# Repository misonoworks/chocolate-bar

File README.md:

# Chocolate Bar

A low-profile 50% keyboard, with less ergonomics than expected!

This keyboard uses choc switches. Choc switches are low-profile switches pioneered by Kailh that use a non-MX style stem. This keyboard uses only standard sizes for choc keycaps, being 1u, 1.5u, and 2u

Please note: V2 PCBs are still compatible with V1 cases and plates. The new feature on the V2 PCB, the OLED, cannot be used on V1 plates or cases. V2 cases do not exist yet, that is currently still being worked on.
V2 firmware is similarly unavailable, though the current firmware should work provided you update the pins. This will be updated after the next proto run.

## Layout

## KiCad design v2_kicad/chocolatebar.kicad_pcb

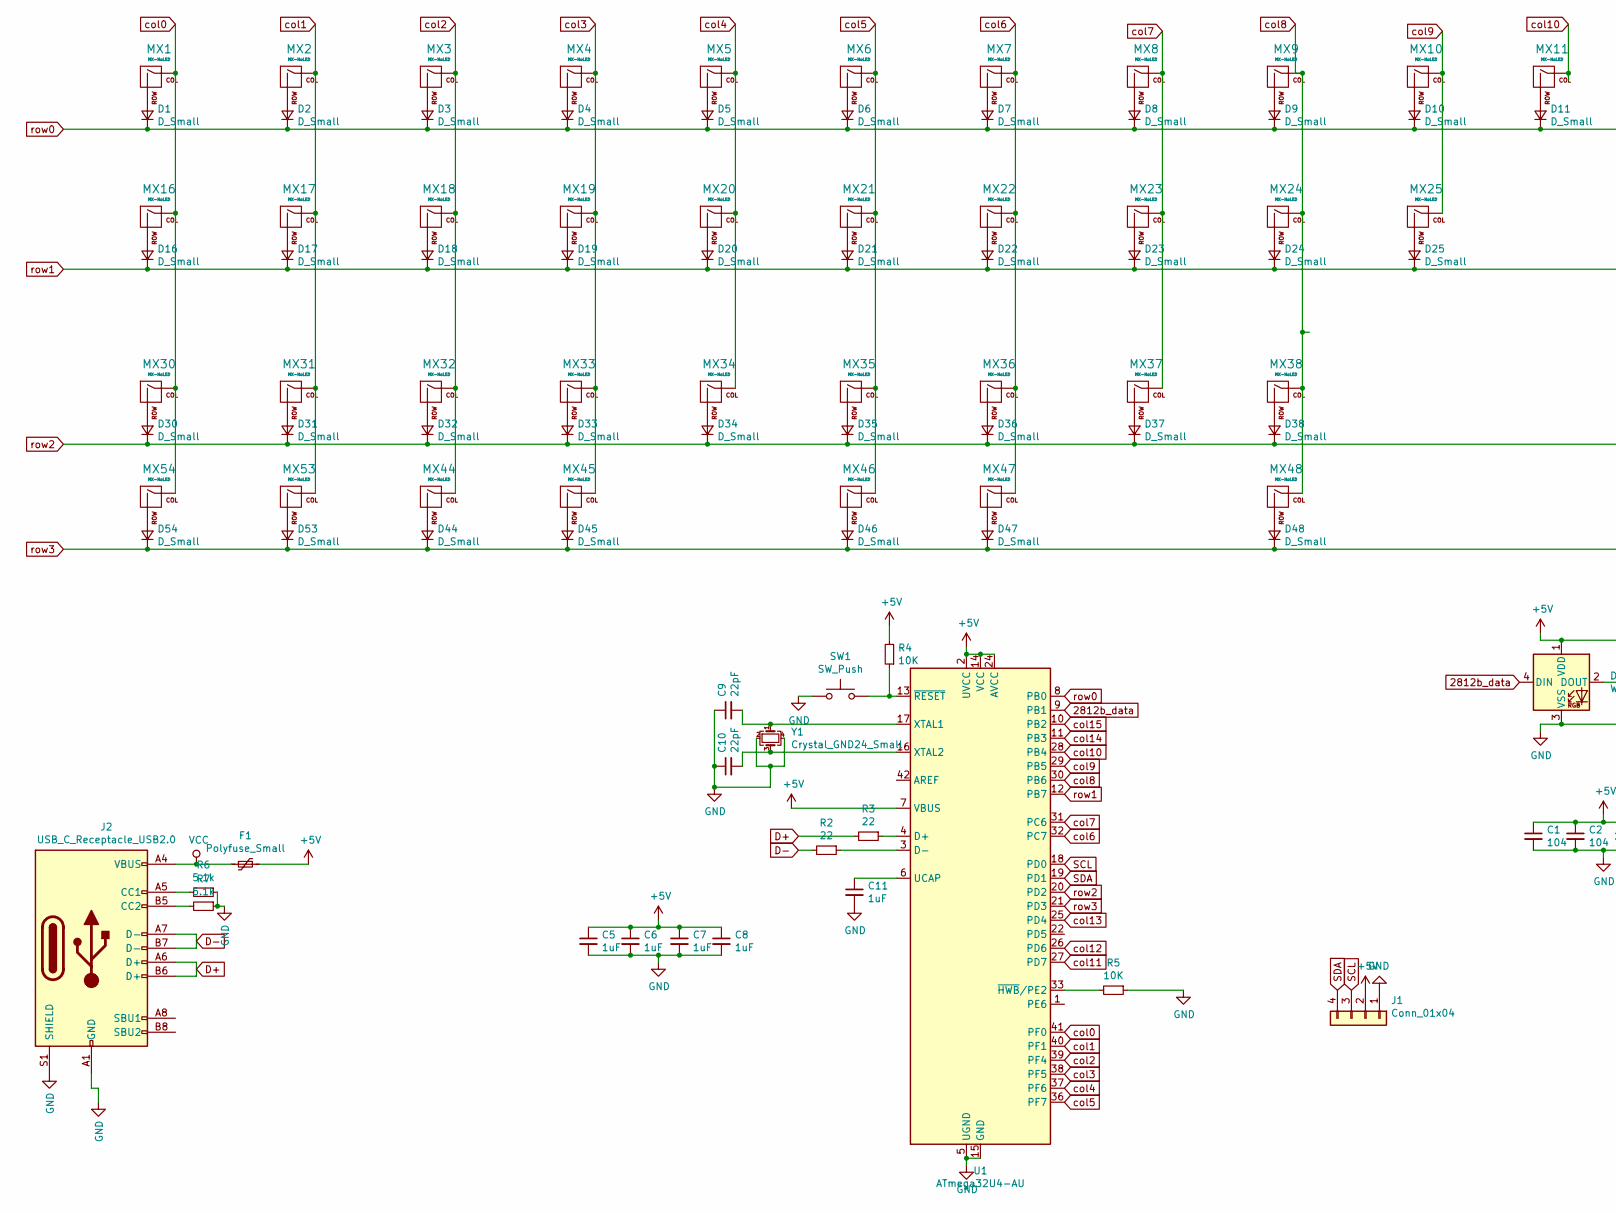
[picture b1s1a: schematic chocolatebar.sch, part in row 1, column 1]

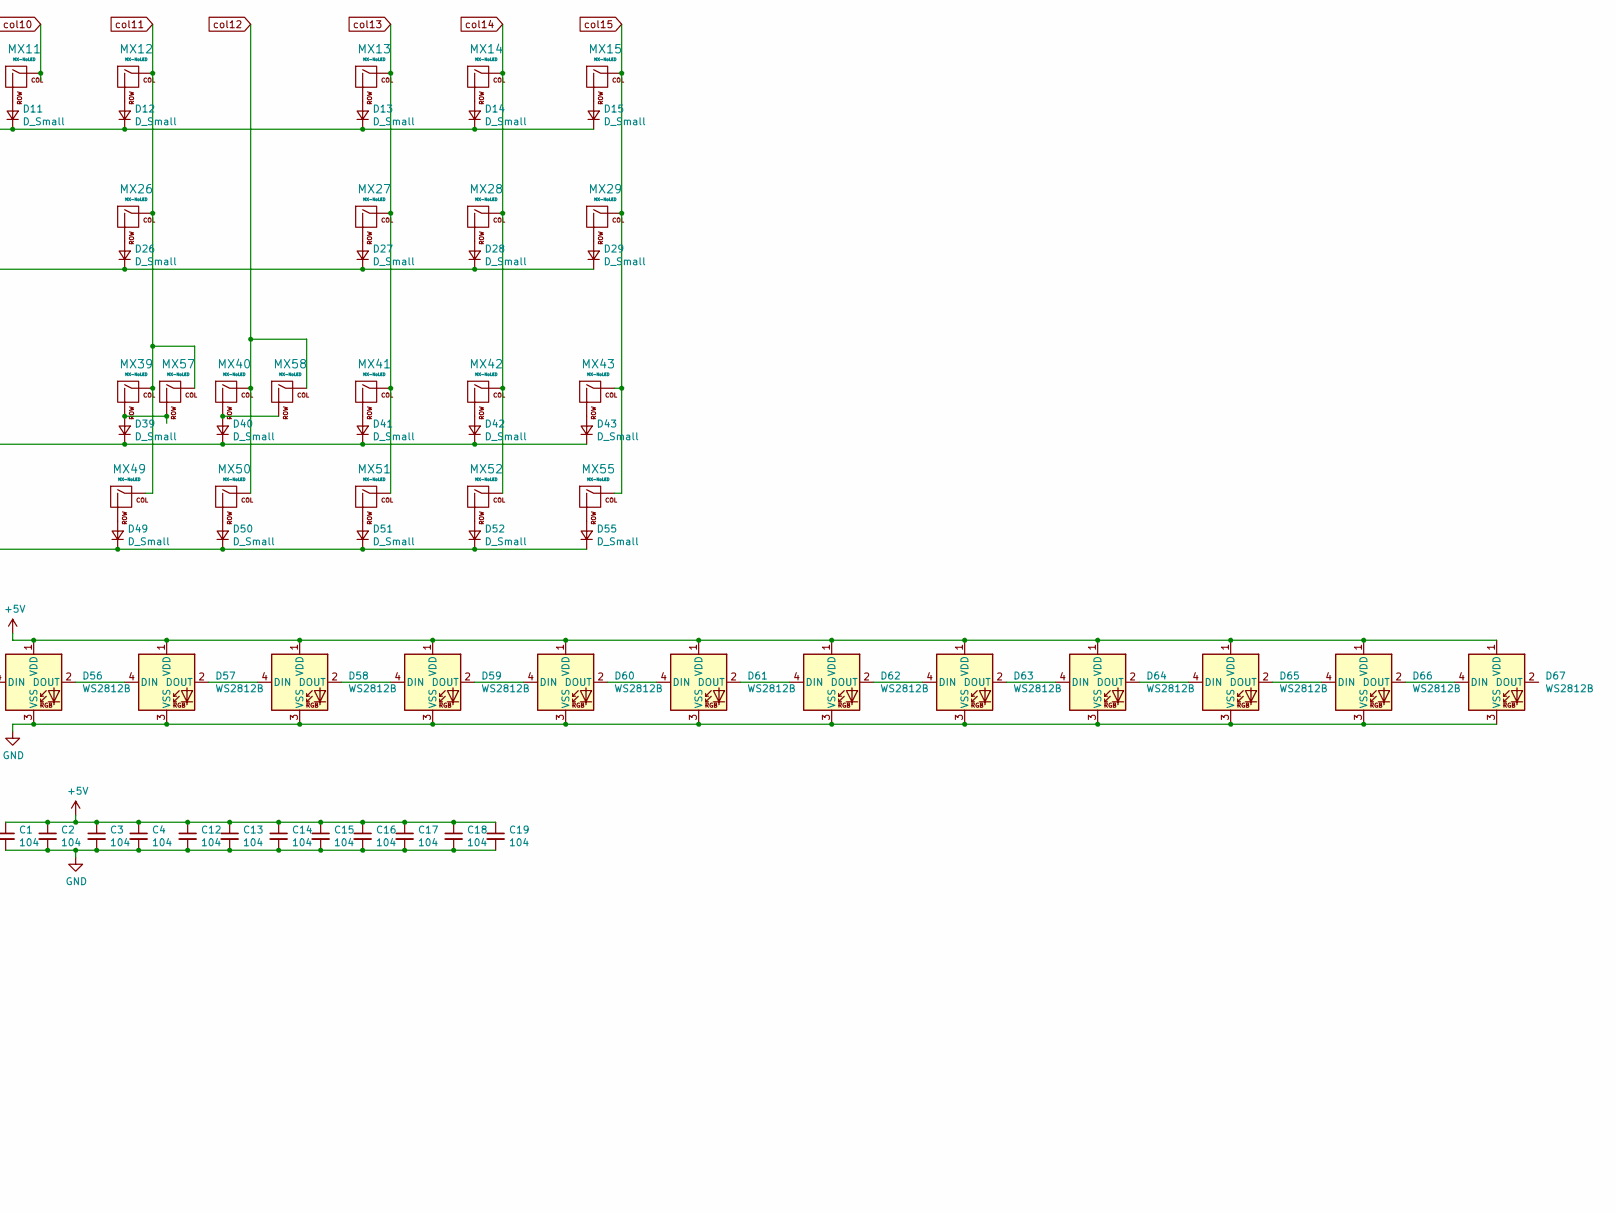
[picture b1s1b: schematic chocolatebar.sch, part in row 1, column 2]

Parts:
C1, C2, C3, C4, C12, C13, C14, C15, C16, C17, C18, C19: 104; C_0805_2012Metric
C5, C6, C7, C8, C11: 1uF; C_0805_2012Metric
C9, C10: 22pF; C_0805_2012Metric
D1, D2, D3, D4, D5, D6, D7, D8, D9, D10, D11, D12, D13, D14, D15, D16, D17, D18, D19, D20, D21, D22, D23, D24, D25, D26, D27, D28, D29, D30, D31, D32, D33, D34, D35, D36, D37, D38, D39, D40, D41, D42, D43, D44, D45, D46, D47, D48, D49, D50, D51, D52, D53, D54, D55: D_Small; D_SOD-123
D56, D57, D58, D59, D60, D61, D62, D63, D64, D65, D66, D67: WS2812B; LED_WS2812B_PLCC4_5.0x5.0mm_P3.2mm
F1: Polyfuse_Small; Fuse_1206_3216Metric
J1: Conn_01x04; PinSocket_1x04_P2.54mm_Vertical
J2: USB_C_Receptacle_USB2.0; USB_C_Receptacle_HRO_TYPE-C-31-M-12
MX1, MX2, MX3, MX4, MX5, MX6, MX7, MX8, MX9, MX10, MX11, MX12, MX13, MX14, MX15, MX16, MX17, MX18, MX19, MX20, MX21, MX22, MX23, MX24, MX25, MX27, MX28, MX29, MX31, MX32, MX33, MX34, MX35, MX36, MX37, MX38, MX39, MX40, MX41, MX42, MX43, MX44, MX47, MX49, MX50, MX51, MX52, MX57, MX58: MX-NoLED; Kailh-PG1350-1u-NoLED
MX26, MX48, MX53, MX54, MX55: MX-NoLED; Kailh-PG1350-1.5u
MX30, MX45, MX46: MX-NoLED; Kailh-PG1350-2u-NoLED
R2, R3: 22; R_0805_2012Metric
R4, R5: 10K; R_0805_2012Metric
R6, R7: 5.1k; R_0805_2012Metric
SW1: SW_Push; SKQG-1155865
U1: ATmega32U4-AU; TQFP-44_10x10mm_P0.8mm
Y1: Crystal_GND24_Small; Crystal_SMD_3225-4Pin_3.2x2.5mm

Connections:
2812b_data: D56.4 (DIN), U1.9 (PB1)
+5V: C1.1, C2.1, C3.1, C4.1, C5.1, C6.1, C7.1, C8.1, C12.1, C13.1, C14.1, C15.1, C16.1, C17.1, C18.1, C19.1, D56.1 (VDD), D57.1 (VDD), D58.1 (VDD), D59.1 (VDD), D60.1 (VDD), D61.1 (VDD), D62.1 (VDD), D63.1 (VDD), D64.1 (VDD), D65.1 (VDD), D66.1 (VDD), D67.1 (VDD), F1.1, J1.2, R4.2, U1.2 (UVCC), U1.7 (VBUS), U1.14 (VCC), U1.24 (AVCC), U1.34 (VCC), U1.44 (AVCC)
D+: J2.A6 (D+), J2.B6 (D+), R3.2
D-: J2.A7 (D-), J2.B7 (D-), R2.2
GND: C1.2, C2.2, C3.2, C4.2, C5.2, C6.2, C7.2, C8.2, C9.1, C10.1, C11.2, C12.2, C13.2, C14.2, C15.2, C16.2, C17.2, C18.2, C19.2, D56.3 (VSS), D57.3 (VSS), D58.3 (VSS), D59.3 (VSS), D60.3 (VSS), D61.3 (VSS), D62.3 (VSS), D63.3 (VSS), D64.3 (VSS), D65.3 (VSS), D66.3 (VSS), D67.3 (VSS), J1.1, J2.A1 (GND), J2.A12 (GND), J2.B1 (GND), J2.B12 (GND), J2.S1 (SHIELD), R5.1, R6.1, R7.1, SW1.1, U1.5 (UGND), U1.15 (GND), U1.23 (GND), U1.35 (GND), U1.43 (GND), Y1.2, Y1.4
unnamed: C9.2, U1.17 (XTAL1), Y1.1
unnamed: C10.2, U1.16 (XTAL2), Y1.3
unnamed: C11.1, U1.6 (UCAP)
unnamed: D1.2 (A), MX1.2 (ROW)
unnamed: D2.2 (A), MX2.2 (ROW)
unnamed: D3.2 (A), MX3.2 (ROW)
unnamed: D4.2 (A), MX4.2 (ROW)
unnamed: D5.2 (A), MX5.2 (ROW)
unnamed: D6.2 (A), MX6.2 (ROW)
unnamed: D7.2 (A), MX7.2 (ROW)
unnamed: D8.2 (A), MX8.2 (ROW)
unnamed: D9.2 (A), MX9.2 (ROW)
unnamed: D10.2 (A), MX10.2 (ROW)
unnamed: D11.2 (A), MX11.2 (ROW)
unnamed: D12.2 (A), MX12.2 (ROW)
unnamed: D13.2 (A), MX13.2 (ROW)
unnamed: D14.2 (A), MX14.2 (ROW)
unnamed: D15.2 (A), MX15.2 (ROW)
unnamed: D16.2 (A), MX16.2 (ROW)
unnamed: D17.2 (A), MX17.2 (ROW)
unnamed: D18.2 (A), MX18.2 (ROW)
unnamed: D19.2 (A), MX19.2 (ROW)
unnamed: D20.2 (A), MX20.2 (ROW)
unnamed: D21.2 (A), MX21.2 (ROW)
unnamed: D22.2 (A), MX22.2 (ROW)
unnamed: D23.2 (A), MX23.2 (ROW)
unnamed: D24.2 (A), MX24.2 (ROW)
unnamed: D25.2 (A), MX25.2 (ROW)
unnamed: D26.2 (A), MX26.2 (ROW)
unnamed: D27.2 (A), MX27.2 (ROW)
unnamed: D28.2 (A), MX28.2 (ROW)
unnamed: D29.2 (A), MX29.2 (ROW)
unnamed: D30.2 (A), MX30.2 (ROW)
unnamed: D31.2 (A), MX31.2 (ROW)
unnamed: D32.2 (A), MX32.2 (ROW)
unnamed: D33.2 (A), MX33.2 (ROW)
unnamed: D34.2 (A), MX34.2 (ROW)
unnamed: D35.2 (A), MX35.2 (ROW)
unnamed: D36.2 (A), MX36.2 (ROW)
unnamed: D37.2 (A), MX37.2 (ROW)
unnamed: D38.2 (A), MX38.2 (ROW)
unnamed: D39.2 (A), MX39.2 (ROW), MX57.2 (ROW)
unnamed: D40.2 (A), MX40.2 (ROW), MX58.2 (ROW)
unnamed: D41.2 (A), MX41.2 (ROW)
unnamed: D42.2 (A), MX42.2 (ROW)
unnamed: D43.2 (A), MX43.2 (ROW)
unnamed: D44.2 (A), MX44.2 (ROW)
unnamed: D45.2 (A), MX45.2 (ROW)
unnamed: D46.2 (A), MX46.2 (ROW)
unnamed: D47.2 (A), MX47.2 (ROW)
unnamed: D48.2 (A), MX48.2 (ROW)
unnamed: D49.2 (A), MX49.2 (ROW)
unnamed: D50.2 (A), MX50.2 (ROW)
unnamed: D51.2 (A), MX51.2 (ROW)
unnamed: D52.2 (A), MX52.2 (ROW)
unnamed: D53.2 (A), MX53.2 (ROW)
unnamed: D54.2 (A), MX54.2 (ROW)
unnamed: D55.2 (A), MX55.2 (ROW)
unnamed: D56.2 (DOUT), D57.4 (DIN)
unnamed: D57.2 (DOUT), D58.4 (DIN)
unnamed: D58.2 (DOUT), D59.4 (DIN)
unnamed: D59.2 (DOUT), D60.4 (DIN)
unnamed: D60.2 (DOUT), D61.4 (DIN)
unnamed: D61.2 (DOUT), D62.4 (DIN)
unnamed: D62.2 (DOUT), D63.4 (DIN)
unnamed: D63.2 (DOUT), D64.4 (DIN)
unnamed: D64.2 (DOUT), D65.4 (DIN)
unnamed: D65.2 (DOUT), D66.4 (DIN)
unnamed: D66.2 (DOUT), D67.4 (DIN)
unnamed: J2.A5 (CC1), R6.2
unnamed: J2.B5 (CC2), R7.2
unnamed: R2.1, U1.3 (D-)
unnamed: R3.1, U1.4 (D+)
unnamed: R4.1, SW1.2, U1.13 (~RESET)
unnamed: R5.2, U1.33 (~HWB~/PE2)
SCL: J1.3, U1.18 (PD0)
SDA: J1.4, U1.19 (PD1)
VCC: F1.2, J2.A4 (VBUS), J2.A9 (VBUS), J2.B4 (VBUS), J2.B9 (VBUS)
col0: MX1.1 (COL), MX16.1 (COL), MX30.1 (COL), MX54.1 (COL), U1.41 (PF0)
col1: MX2.1 (COL), MX17.1 (COL), MX31.1 (COL), MX53.1 (COL), U1.40 (PF1)
col2: MX3.1 (COL), MX18.1 (COL), MX32.1 (COL), MX44.1 (COL), U1.39 (PF4)
col3: MX4.1 (COL), MX19.1 (COL), MX33.1 (COL), MX45.1 (COL), U1.38 (PF5)
col4: MX5.1 (COL), MX20.1 (COL), MX34.1 (COL), U1.37 (PF6)
col5: MX6.1 (COL), MX21.1 (COL), MX35.1 (COL), MX46.1 (COL), U1.36 (PF7)
col6: MX7.1 (COL), MX22.1 (COL), MX36.1 (COL), MX47.1 (COL), U1.32 (PC7)
col7: MX8.1 (COL), MX23.1 (COL), MX37.1 (COL), U1.31 (PC6)
col8: MX9.1 (COL), MX24.1 (COL), MX38.1 (COL), MX48.1 (COL), U1.30 (PB6)
col9: MX10.1 (COL), MX25.1 (COL), U1.29 (PB5)
col10: MX11.1 (COL), U1.28 (PB4)
col11: MX12.1 (COL), MX26.1 (COL), MX39.1 (COL), MX49.1 (COL), MX57.1 (COL), U1.27 (PD7)
col12: MX40.1 (COL), MX50.1 (COL), MX58.1 (COL), U1.26 (PD6)
col13: MX13.1 (COL), MX27.1 (COL), MX41.1 (COL), MX51.1 (COL), U1.25 (PD4)
col14: MX14.1 (COL), MX28.1 (COL), MX42.1 (COL), MX52.1 (COL), U1.11 (PB3)
col15: MX15.1 (COL), MX29.1 (COL), MX43.1 (COL), MX55.1 (COL), U1.10 (PB2)
row0: D1.1 (K), D2.1 (K), D3.1 (K), D4.1 (K), D5.1 (K), D6.1 (K), D7.1 (K), D8.1 (K), D9.1 (K), D10.1 (K), D11.1 (K), D12.1 (K), D13.1 (K), D14.1 (K), D15.1 (K), U1.8 (PB0)
row1: D16.1 (K), D17.1 (K), D18.1 (K), D19.1 (K), D20.1 (K), D21.1 (K), D22.1 (K), D23.1 (K), D24.1 (K), D25.1 (K), D26.1 (K), D27.1 (K), D28.1 (K), D29.1 (K), U1.12 (PB7)
row2: D30.1 (K), D31.1 (K), D32.1 (K), D33.1 (K), D34.1 (K), D35.1 (K), D36.1 (K), D37.1 (K), D38.1 (K), D39.1 (K), D40.1 (K), D41.1 (K), D42.1 (K), D43.1 (K), U1.20 (PD2)
row3: D44.1 (K), D45.1 (K), D46.1 (K), D47.1 (K), D48.1 (K), D49.1 (K), D50.1 (K), D51.1 (K), D52.1 (K), D53.1 (K), D54.1 (K), D55.1 (K), U1.21 (PD3)

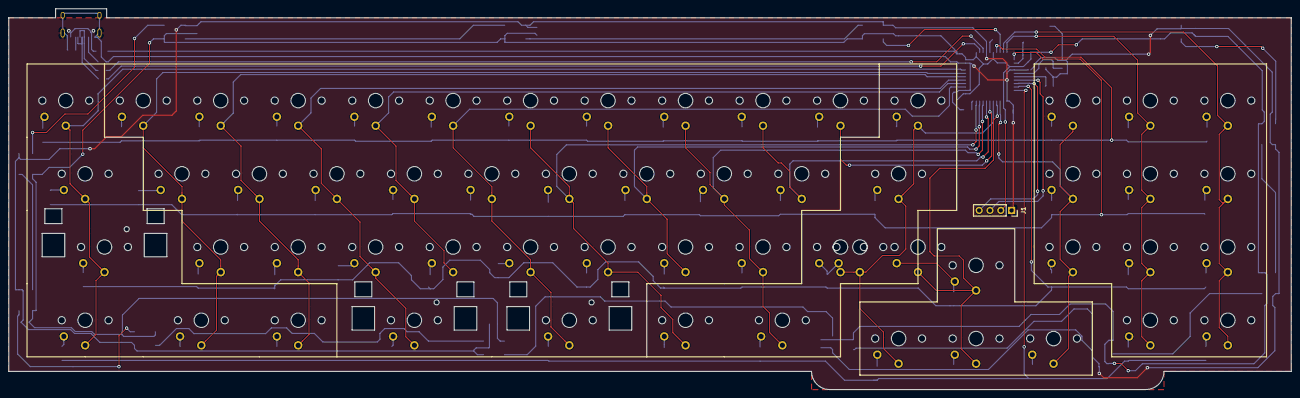
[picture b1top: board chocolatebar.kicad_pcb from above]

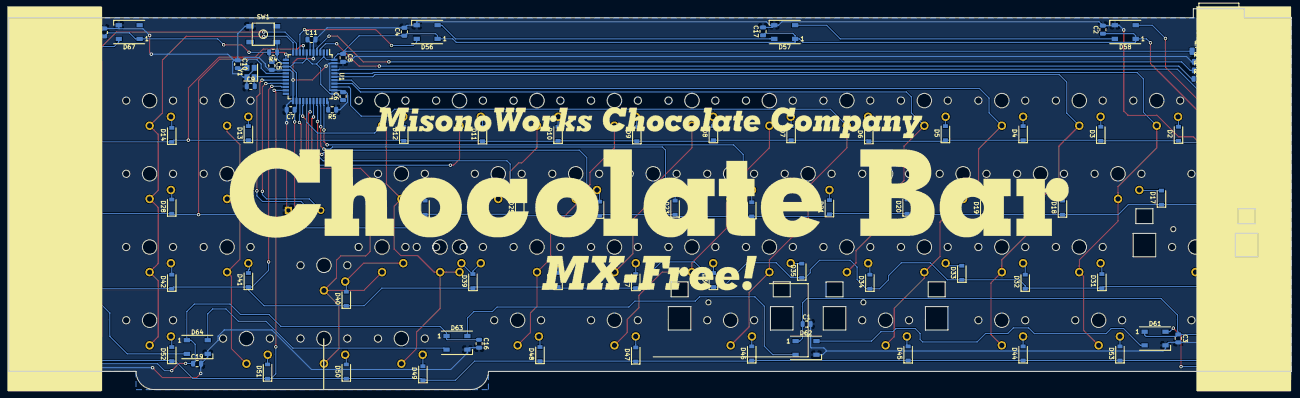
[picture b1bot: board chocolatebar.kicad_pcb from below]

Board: 2 copper layers, 301.3 x 89.4 mm, 155 parts (97 on the bottom side), 103 nets.

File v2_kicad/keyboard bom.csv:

"Id";"Designator";"Package";"Quantity";"Designation";"Supplier and ref";
1;"D52,D57,D56,D55,D54,D53,D51,D50,D49,D48,D47,D46,D45,D44,D43,D4,D3,D2,D1";"LED_WS2812B_PLCC4_5.0x5.0mm_P3.2mm";19;"WS2812B";;;
2;"SW3,SW2";"RotaryEncoder_Alps_EC12E-Switch_Vertical_H20mm";2;"Rotary_Encoder_Switch";;;
3;"D59,D58,D42,D41,D40,D39,D38,D37,D36,D35,D34,D33,D32,D31,D30,D29,D28,D27,D26,D25,D24,D23,D22,D21,D20,D19,D18,D17,D16,D15,D14,D13,D12,D11,D10,D9,D8,D7,D6,D5";"D_SOD-123";40;"D_Small";;;
4;"C26,C25,C24,C23,C22,C21,C20,C19,C18,C17,C16,C15,C14,C13,C12,C4,C3,C2,C1";"C_0805_2012Metric";19;"104";;;
5;"R1";"R_0805_2012Metric";1;"500ohm";;;
6;"C5,C11,C8,C7,C6";"C_0805_2012Metric";5;"1uF";;;
7;"K_Z1,K_Y1,K_X1,K_W1,K_V1,K_U1,K_TAB1,K_T1,K_S1,K_R1,K_Q1,K_PERIOD1,K_P1,K_O1,K_N1,K_M1,K_L1,K_K1,K_J1,K_I1,K_H1,K_G1,K_F1,K_E1,K_D1,K_C1,K_B1,K_APO1,K_A1";"MX-1U-NoLED";29;"MX-NoLED";;;
8;"K_SUPER1,K_SPBALT1";"MX-1.25U-NoLED";2;"MX-NoLED";;;
9;"K_SPBSPACE1";"MX-2.75U-ReversedStabilizers-NoLED";1;"MX-NoLED";;;
10;"K_SPBDEL1";"MX-2.25U-ReversedStabilizers-NoLED";1;"MX-NoLED";;;
11;"K_SPACEBARSIX1";"MX-6.25U-ReversedStabilizers-NoLED";1;"MX-NoLED";;;
12;"K_SHIFT2,K_SHIFT1";"MX-1.5U-NoLED";2;"MX-NoLED";;;
13;"K_META1,K_LCTRL1";"MX-1.75U-NoLED";2;"MX-NoLED";;;
14;"Y1";"Crystal_SMD_3225-4Pin_3.2x2.5mm";1;"Crystal_GND24_Small";;;
15;"USB1";"HRO-TYPE-C-31-M-12-HandSoldering";1;"HRO-TYPE-C-31-M-12";;;
16;"U1";"TQFP-44_10x10mm_P0.8mm";1;"ATmega32U4-AU";;;
17;"SW1";"SKQG-1155865";1;"SW_Push";;;
18;"R7,R6";"R_0805_2012Metric";2;"5.1k";;;
19;"R5,R4";"R_0805_2012Metric";2;"10K";;;
20;"R3,R2";"R_0805_2012Metric";2;"22";;;
21;"F1";"Fuse_1206_3216Metric";1;"Polyfuse_Small";;;
22;"C10,C9";"C_0805_2012Metric";2;"22pF";;;

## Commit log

2020-11-30 added kicad source
2020-11-30 added via support (created by dezli)
2021-08-17 V2 update
2021-09-28 update hexfiles
